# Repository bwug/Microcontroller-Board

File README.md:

<h1>Microcontroller Board</h1>
<h6>Designed for signal integrity</h6>

This board connects a _PIC16_ or _PIC18_ microcontroller to a series of LED and resistor combos, this board was designed for university work though is more than viable for real-world testing applications due to the simplicity of individual pin testing

The goal of this design was to produce a small board which used different design principles taught throughout first semester to have great signal integrity

Use [KiCanvas](https://kicanvas.org/) to view the board, the [PCB](https://kicanvas.org/?github=https%3A%2F%2Fgithub.com%2Fbwug%2FMicrocontroller-Board%2Fblob%2Fmain%2Fsignal_board.kicad_pcb) can be seen here and the [schematic](https://kicanvas.org/?github=https%3A%2F%2Fgithub.com%2Fbwug%2FMicrocontroller-Board%2Fblob%2Fmain%2Fsignal_board.kicad_sch) here.

This project helped me develop my skills in developing boards when conciously thinking about the signals used throughout the circuit, as well as designing with a philosophy of "If someone uses this, will they be able to solder onto it?"

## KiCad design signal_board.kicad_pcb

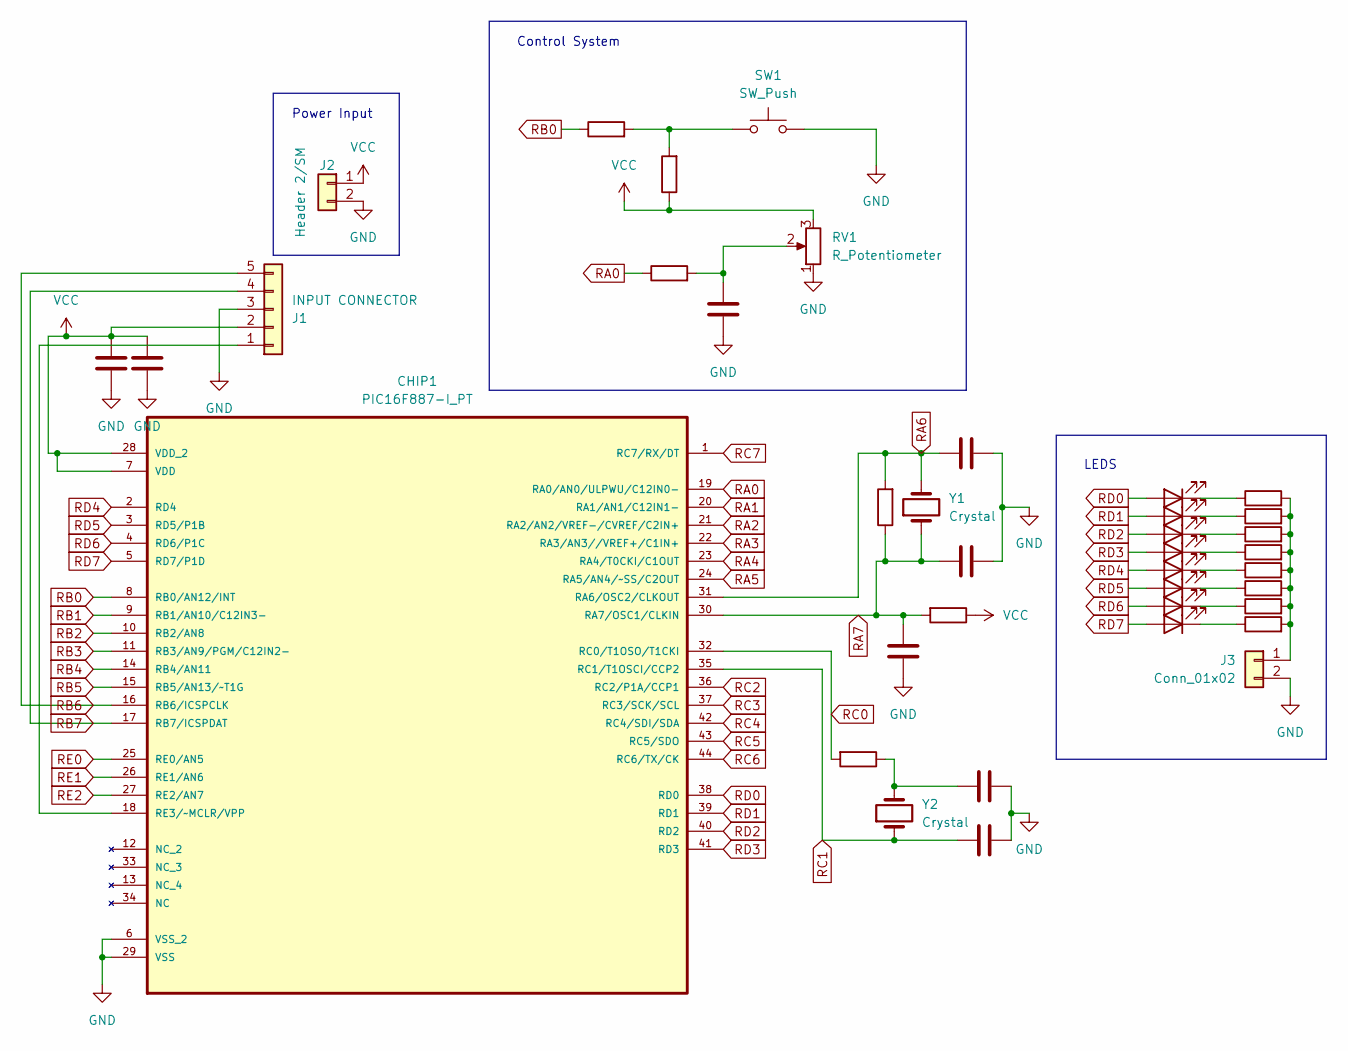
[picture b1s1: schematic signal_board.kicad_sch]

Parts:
C1, C2, C3, C4, C5, C6, C7, C8: C; C_0805_2012Metric
CHIP1: PIC16F887-I_PT; LQFP-44_10x10mm_P0.8mm; MPN PIC16F887-I/PT
D1, D2, D3, D4, D5, D6, D7, D8: LED; D_0805_2012Metric
J1: INPUT CONNECTOR; PinSocket_1x05_P2.54mm_Vertical
J2: Header 2/SM; PinSocket_1x02_P2.54mm_Vertical
J3: Conn_01x02; PinSocket_1x02_P2.54mm_Vertical
R1, R2, R3, R4, R5, R6, R7, R8: 750; R_0805_2012Metric
R9, R11: 1k; R_0805_2012Metric
R10, R13: 10k; R_0805_2012Metric
R12: 1M; R_0805_2012Metric
R14: 220k; R_0805_2012Metric
RV1: R_Potentiometer; Potentiometer_ACP_CA6-H2,5_Horizontal
SW1: SW_Push; SW_Push_1P1T_XKB_TS-1187A
Y1, Y2: Crystal; Crystal_SMD_0603-2Pin_6.0x3.5mm

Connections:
GND: C1.2, C2.2, C3.2, C4.1, C5.1, C6.1, C7.1, C8.1, CHIP1.6 (VSS_2), CHIP1.29 (VSS), J1.3, J2.2, J3.2, RV1.1, SW1.2
unnamed: C2.1, R9.2, RV1.2
unnamed: C7.2, R14.1, Y2.2
unnamed: CHIP1.18 (RE3/~MCLR/VPP), J1.1
unnamed: D1.1 (K), R1.1
unnamed: D2.1 (K), R2.1
unnamed: D3.1 (K), R3.1
unnamed: D4.1 (K), R4.1
unnamed: D5.1 (K), R5.1
unnamed: D6.1 (K), R6.1
unnamed: D7.1 (K), R7.1
unnamed: D8.1 (K), R8.1
unnamed: J3.1, R1.2, R2.2, R3.2, R4.2, R5.2, R6.2, R7.2, R8.2
unnamed: R10.2, R11.2, SW1.1
RA0: CHIP1.19 (RA0/AN0/ULPWU/C12IN0-), R9.1
RA1: CHIP1.20 (RA1/AN1/C12IN1-)
RA2: CHIP1.21 (RA2/AN2/VREF-/CVREF/C2IN+)
RA3: CHIP1.22 (RA3/AN3//VREF+/C1IN+)
RA4: CHIP1.23 (RA4/T0CKI/C1OUT)
RA5: CHIP1.24 (RA5/AN4/~SS/C2OUT)
RA6: C1.1, CHIP1.31 (RA6/OSC2/CLKOUT), R12.2, Y1.2
RA7: C3.1, C4.2, CHIP1.30 (RA7/OSC1/CLKIN), R12.1, R13.2, Y1.1
RB0: CHIP1.8 (RB0/AN12/INT), R11.1
RB1: CHIP1.9 (RB1/AN10/C12IN3-)
RB2: CHIP1.10 (RB2/AN8)
RB3: CHIP1.11 (RB3/AN9/PGM/C12IN2-)
RB4: CHIP1.14 (RB4/AN11)
RB5: CHIP1.15 (RB5/AN13/~T1G)
RB6: CHIP1.16 (RB6/ICSPCLK), J1.5
RB7: CHIP1.17 (RB7/ICSPDAT), J1.4
RC0: CHIP1.32 (RC0/T1OSO/T1CKI), R14.2
RC1: C8.2, CHIP1.35 (RC1/T1OSCI/CCP2), Y2.1
RC2: CHIP1.36 (RC2/P1A/CCP1)
RC3: CHIP1.37 (RC3/SCK/SCL)
RC4: CHIP1.42 (RC4/SDI/SDA)
RC5: CHIP1.43 (RC5/SDO)
RC6: CHIP1.44 (RC6/TX/CK)
RC7: CHIP1.1 (RC7/RX/DT)
RD0: CHIP1.38 (RD0), D1.2 (A)
RD1: CHIP1.39 (RD1), D2.2 (A)
RD2: CHIP1.40 (RD2), D3.2 (A)
RD3: CHIP1.41 (RD3), D4.2 (A)
RD4: CHIP1.2 (RD4), D5.2 (A)
RD5: CHIP1.3 (RD5/P1B), D6.2 (A)
RD6: CHIP1.4 (RD6/P1C), D7.2 (A)
RD7: CHIP1.5 (RD7/P1D), D8.2 (A)
RE0: CHIP1.25 (RE0/AN5)
RE1: CHIP1.26 (RE1/AN6)
RE2: CHIP1.27 (RE2/AN7)
VCC: C5.2, C6.2, CHIP1.7 (VDD), CHIP1.28 (VDD_2), J1.2, J2.1, R10.1, R13.1, RV1.3

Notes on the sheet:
Control System
Power Input
LEDS

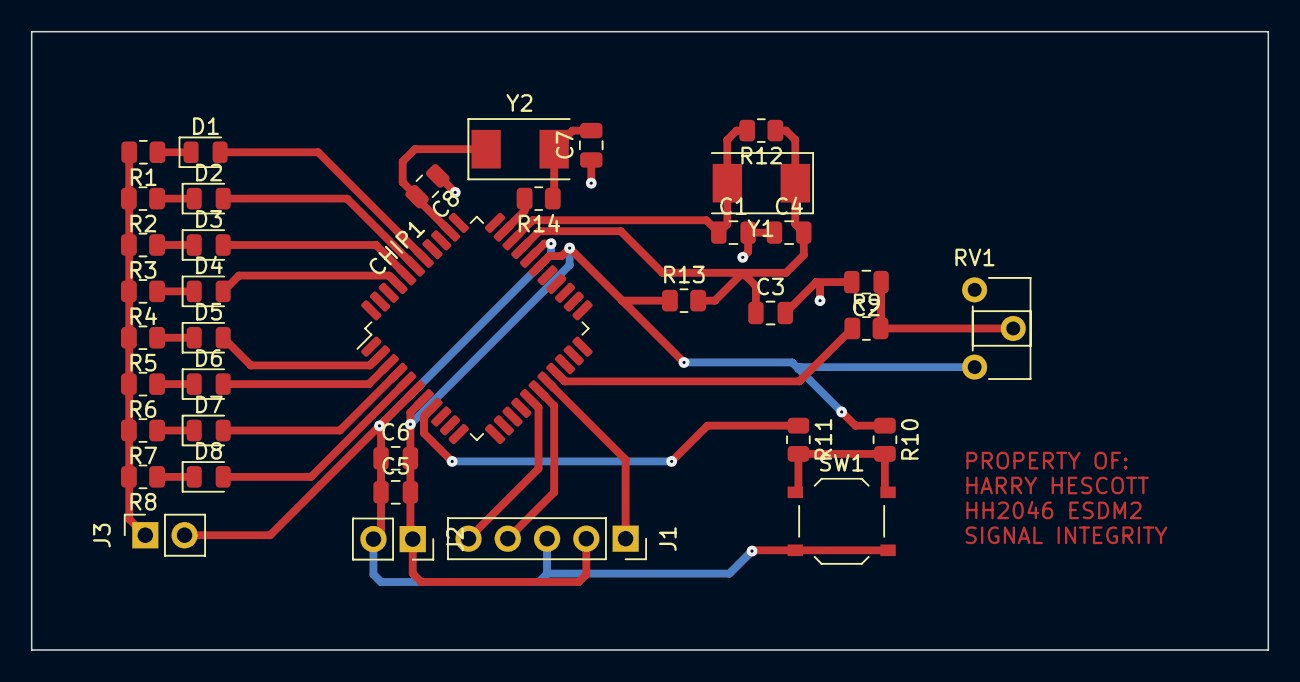
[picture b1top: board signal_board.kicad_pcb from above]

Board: 2 copper layers, 80.0 x 40.0 mm, 38 parts (0 on the bottom side), 31 nets.

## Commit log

2024-10-18 Updated and formatted the readme
